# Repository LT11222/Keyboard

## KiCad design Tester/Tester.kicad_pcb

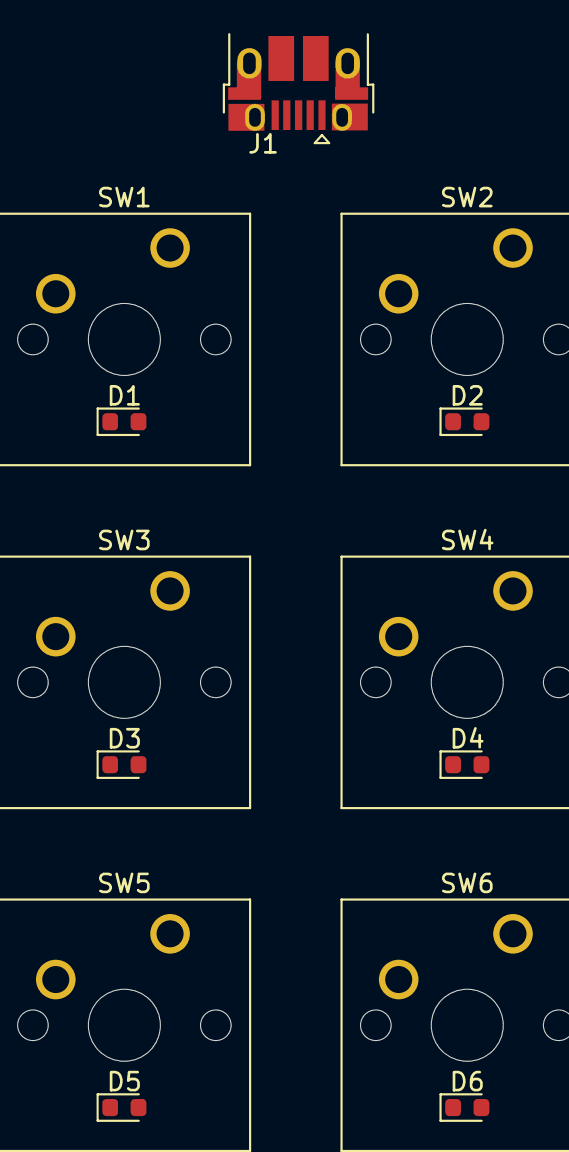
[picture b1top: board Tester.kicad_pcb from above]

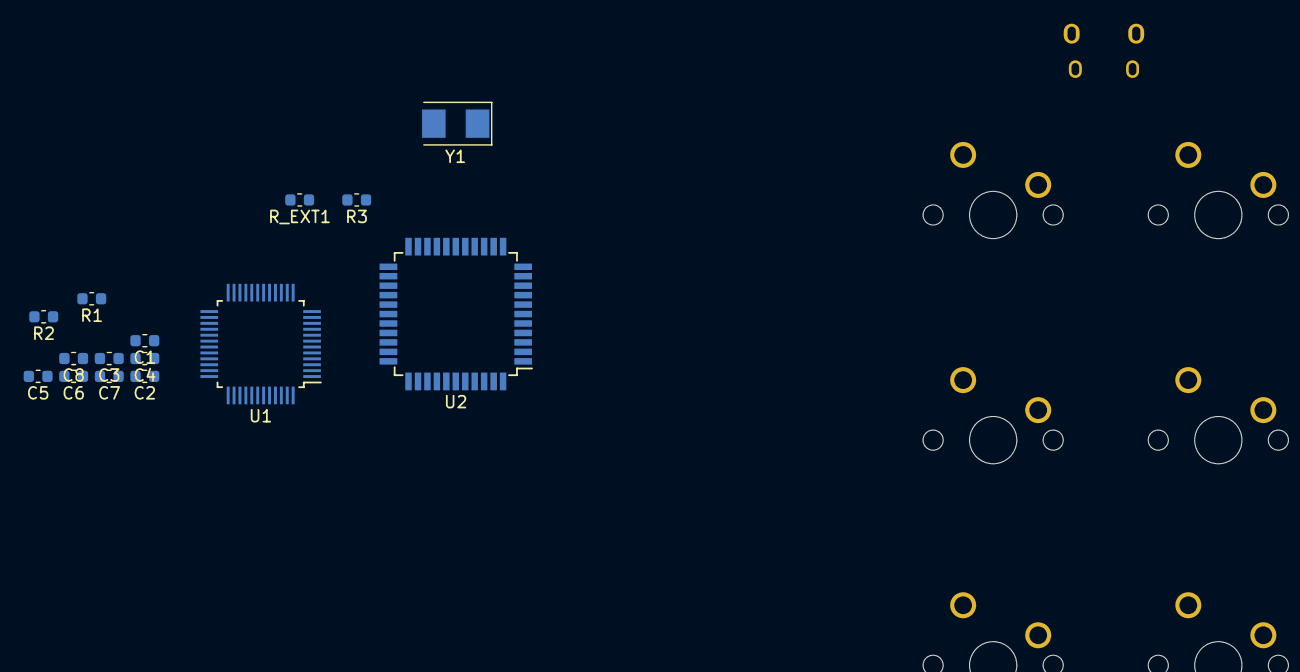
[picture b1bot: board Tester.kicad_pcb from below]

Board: 2 copper layers, 28 parts (15 on the bottom side), 22 nets, no tracks yet.

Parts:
C1, C2, C3, C4: 0.1pF; C_0603_1608Metric
C5, C8: 1uF; C_0603_1608Metric
C6, C7: 22pF; C_0603_1608Metric
D1, D2, D3, D4, D5, D6: 1N4148; D_0603_1608Metric
J1: USB_B_Micro; USB_Micro-B_Amphenol_10103594-0001LF_Horizontal
R1: 100kΩ; R_0603_1608Metric
R2, R3: 1kΩ; R_0603_1608Metric
R_EXT1: 20kΩ; R_0603_1608Metric
SW1, SW2, SW3, SW4, SW5, SW6: SW_Push; SW_Cherry_MX1A_1.00u_PCB
U1: IS31FL3733
U2: ATmega32U4-AU; TQFP-44_10x10mm_P0.8mm
Y1: 16Mhz Crystal; Crystal_SMD_5032-2Pin_5.0x3.2mm

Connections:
Col1: SW1.1, SW2.1, SW3.1, U2.29
Col2: SW4.1, SW5.1, SW6.1, U2.28
Earth: C1.2, C2.1, C3.1, C4.1, C5.2, C6.2, C7.2, C8.2, J1.5, J1.6, R1.1, R_EXT1.1, U1.5, U1.12, U1.34, U1.43, U1.44, U1.48, U2.5, U2.15, U2.23, U2.35, U2.43
unnamed: C6.1, U2.17, Y1.1
unnamed: C7.1, U2.16, Y1.2
unnamed: C8.1, U2.6
unnamed: D1.2, SW1.2
unnamed: D2.2, SW2.2
unnamed: D3.2, SW3.2
unnamed: D4.2, SW4.2
unnamed: D5.2, SW5.2
unnamed: D6.2, SW6.2
unnamed: J1.2, U2.3
unnamed: J1.3, U2.4
unnamed: R1.2, U1.47
unnamed: R_EXT1.2, U1.35
Row1: D1.1, D4.1, U2.20
Row2: D2.1, D5.1, U2.21
Row3: D3.1, D6.1, U2.25
SCL: R3.1, U1.42, U2.18
SDA: R2.1, U1.41, U2.19
VCC: C1.1, C2.2, C3.2, C4.2, C5.1, J1.1, R2.2, R3.2, U1.20, U1.29, U1.37, U1.38, U1.39, U1.46, U2.2, U2.7, U2.14, U2.24, U2.34, U2.44
